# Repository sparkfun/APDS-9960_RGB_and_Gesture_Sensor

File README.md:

SparkFun APDS-9960 RGB and Gesture Sensor
========================================

[*SparkFun APDS-9960 Breakout Board (SEN-12787)*](https://www.sparkfun.com/products/12787)

This is the SparkFun RGB and Gesture Sensor, a small breakout board with a built in APDS-9960 sensor that offers ambient light and color measuring, proximity detection, and touchless gesture sensing.
With this RGB and Gesture Sensor you will be able to control a computer, microcontroller, robot, and more with a simple swipe of your hand! 

 Repository Contents
-------------------

* **/Hardware** - Eagle design files (.brd, .sch)
* **/Libraries** - Libraries for use with the SparkFun APDS9960 RGB and Gesture Sensor
* **/Production** - Production panel files (.brd)

Documentation
--------------
* **[Quickstart Guide](https://learn.sparkfun.com/tutorials/apds-9960-rgb-and-gesture-sensor-hookup-guide)** - Basic hookup guide for the sensor.
* **[Library/README](https://github.com/sparkfun/SparkFun_APDS-9960_Sensor_Arduino_Library/tree/V_1.4.1)** - Arduino library for the SparkFun_APDS9960 RGB and Gesture Sensor.
* **[SparkFun Fritzing repo](https://github.com/sparkfun/Fritzing_Parts)** - Fritzing diagrams for SparkFun products.
* **[SparkFun 3D Model repo](https://github.com/sparkfun/3D_Models)** - 3D models of SparkFun products. 

Product Versions
----------------
* **[SEN-12787](https://www.sparkfun.com/products/12787)** - APDS-9960 RGB and Gesture Sensor

Version History
---------------
* [V_H1.0_L1.4.2](https://github.com/sparkfun/APDS-9960_RGB_and_Gesture_Sensor/tree/V_H1.0_L1.4.2) - Fixing library name compiliation error. 
* [V_H1.0_L1.4.1](https://github.com/sparkfun/APDS-9960_RGB_and_Gesture_Sensor/tree/V_H1.0_L1.4.1) - Fixing minor typos in both library and hardware files.
* [V_1.1.1](https://github.com/sparkfun/APDS-9960_RGB_and_Gesture_Sensor/tree/V_1.1.1) - Updated to new tag syntax
* [V11](https://github.com/sparkfun/APDS-9960_RGB_and_Gesture_Sensor/tree/v11) - Updated to new library structure
* [v10](https://github.com/sparkfun/APDS-9960_RGB_and_Gesture_Sensor/tree/v10) - Release
* [v01](https://github.com/sparkfun/APDS-9960_RGB_and_Gesture_Sensor/tree/v01)

License Information
-------------------
This product is _**open source**_! 

The **hardware** is released under [Creative Commons ShareAlike 4.0 International](https://creativecommons.org/licenses/by-sa/4.0/).

The **code** is beerware; if you see me (or any other SparkFun employee) at the local, and you've found our code helpful, please buy us a round!

Please use, reuse, and modify these files as you see fit. Please maintain attribution to SparkFun Electronics and release anything derivative under the same license.

Distributed as-is; no warranty is given.

- Your friends at SparkFun.

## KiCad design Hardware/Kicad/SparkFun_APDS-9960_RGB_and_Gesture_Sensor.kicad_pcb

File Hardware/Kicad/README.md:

# What Are these Files?

These are Kicad hardware files, gerber files, and renders of the design. Created by [WyoLum](https://wyolum.com/).

# License

This product is open source! These Eagle files are released under the Creative Commons Share-Alike Attribution license ([CC BY-SA 3.0](http://creativecommons.org/licenses/by-sa/3.0/us/)).

Please use, reuse, and modify these files as you see fit. Please maintain attribution and release anything derivative under the same license.

- Your friends at SparkFun.

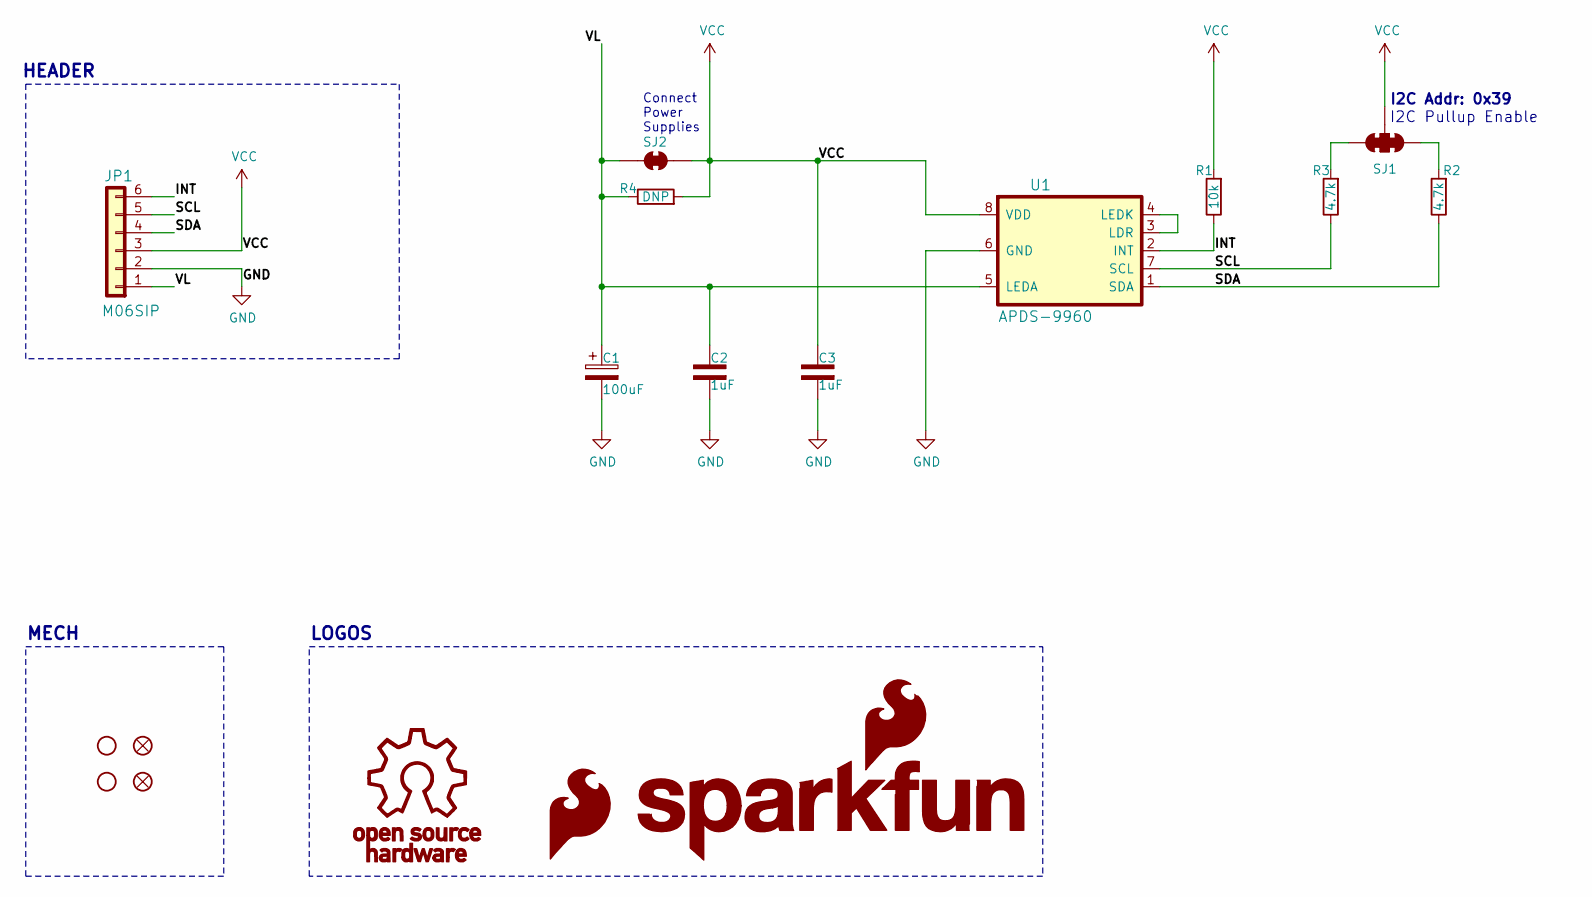
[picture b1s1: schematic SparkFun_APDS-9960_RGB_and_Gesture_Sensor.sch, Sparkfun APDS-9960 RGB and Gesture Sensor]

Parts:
C1: 100uF; c_2917
C2, C3: 1uF; 0603-CAP
FID1, FID2: FIDUCIAL1X2; FIDUCIAL-1X2
JP1: M06SIP; 1X06
LOGO1: SFE_LOGO_FLAME.1_INCH; SFE_LOGO_NAME_FLAME_.1
LOGO2: OSHW-LOGOS; OSHW-LOGO-S
R1: 10k; 0603-RES
R2, R3: 4.7k; 0603
R4: DNP; 0603-RES
SJ1: SOLDERJUMPER_2WAYPASTE1&2&3; SJ_3_PASTE1&2&3
SJ2: SOLDERJUMPERNC; SJ_2S
STANDOFF1, STANDOFF2: STAND-OFF
U1: APDS-9960
U$1: SFE_LOGO_NAME_FLAME.1_INCH; SFE_LOGO_FLAME_.1

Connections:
/INT: JP1.6, R1.1, U1.2 (INT)
/SCL: JP1.5, R3.1, U1.7 (SCL)
/SDA: JP1.4, R2.1, U1.1 (SDA)
/VL: C1.1, C2.1, JP1.1, R4.1, SJ2.1, U1.5 (LEDA)
GND: C1.2, C2.2, C3.2, JP1.2, U1.6 (GND)
unnamed: R2.2, SJ1.3
unnamed: R3.2, SJ1.1
unnamed: U1.3 (LDR), U1.4 (LEDK)
VCC: C3.1, JP1.3, R1.2, R4.2, SJ1.2, SJ2.2, U1.8 (VDD)

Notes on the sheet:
I2C Addr: 0x39
I2C Pullup Enable
Connect Power Supplies
MECH
LOGOS
HEADER

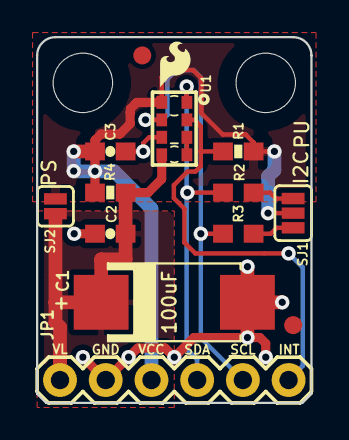
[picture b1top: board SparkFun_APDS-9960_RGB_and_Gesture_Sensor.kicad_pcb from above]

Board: 2 copper layers, 15.2 x 20.3 mm, 18 parts (0 on the bottom side), 9 nets.

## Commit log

2014-03-03 Added initial README and LICENSE files
2014-03-03 Created schematic for breakout board
2014-03-05 Created initial layout
2014-03-05 Added SS text
2014-03-05 Added name on layout
2014-03-05 Replaced 4.7k INT pullup with 10k
2014-03-12 Rotated OSHW logo and added I2C address to sch and silk.
2014-04-15 Test commit with account
2014-05-14 Added separate VLED (VL) pin, connected VL and VCC with solder jumper and optional resistor. Re-did layout to support new features.
2014-05-14 Fixed text font and size on schematic
2014-05-30 Added skeleton library
2014-05-30 Renamed library SFE_APDS-9960 to SFE_APDS9960
2014-06-04 Created skeleton library and ProximityTest example
2014-06-07 Added first part of init function. Still need to finish default register values.
2014-06-08 Added init code for prox and ALS registers
2014-06-09 Added led gain control and photodiode mask methods
2014-07-03 Updated library. Can now read gesture FIFO.
2014-07-06 Added readGesture method. It sorta works.
2014-07-06 Fixed gesture sensing. Works like the Avago demo now.
2014-07-07 Fixed gesture return values for U/D/L/R and gestureTest example.
2014-07-15 Updated version number to v10 for reds
2014-07-15 created panel v10
2014-10-15 Fixed buffer overflow issue with block reads. This fixed the problems with reading NEAR and FAR gestures.
2014-10-23 Added outline for color sensing code
2014-10-23 Moved several get/set methods to public. Added power on/off method.
2014-10-24 Added methods to control light sensor and light sensor demo sketch.
2014-10-27 Added color (RGB) light sensing example.
2014-10-27 Added methods for controlling ambient light interrupt thresholds.
2014-10-28 Finished interrupt demos for the library.
2014-10-28 Readme added to library
2014-10-28 Fixed some misspellings in the library readme.
2014-11-03 Added PDF of schematic
2014-11-04 Updated READMEs with license and folder information
2014-11-05 Changed the names of files and Arduino libraries to contain 'SparkFun_' as a prefix
2014-11-07 Added known issue to library regarding the freezing on fast gestures
2014-11-14 Fixed freezing issue with fast swipes
2014-11-18 Added pinMode like to GestureTest.ino example to fix interrupt not working with some Arduinos.
2014-12-15 Suggestions For Possible Board Revision
    I have a few suggestions to make this board work better in my
    application.
    I'm a noob with GitHub, so I appologise if I'm doing this wrong.
    Changes:
    1) Rotate and relocate sensor as close as possible to edge of board.
    Reason: I want to be able to put this sensor board into an enclosure
2015-01-14 Implemented disableProximitySensor()
2015-02-04 Changed 4.7k resistors to proper 0603-RES package.
    This adds a small silkscreen dot under the resistor.
2015-02-05 Reverting to current board layout files
2015-04-26 Squashed 'Libraries/Arduino/' content from commit cb761c9
    git-subtree-dir: Libraries/Arduino
    git-subtree-split: cb761c9f0f9f36acc54a8502904df46fbca3fc06
2015-04-26 Updated to new library structure
2015-04-29 Part of the new arduino lib format updates
2015-04-29 commited
2015-04-29 Squashed 'Libraries/Arduino/' content from commit d35b342
    git-subtree-dir: Libraries/Arduino
    git-subtree-split: d35b342f01b4587b4a9401d6ab1262f9d95b321b
2015-05-13 Squashed 'Libraries/Arduino/' changes from d35b342..e60af2c
    git-subtree-dir: Libraries/Arduino
    git-subtree-split: e60af2cdf0042a4ac6cdcac1a4fe5b38b0d575b7
2015-05-13 Updating documentation, adding git attributes
2015-07-21 Squashed 'Libraries/Arduino/' changes from e60af2c..347a7d5
    347a7d5 Updating library name
    git-subtree-dir: Libraries/Arduino
    git-subtree-split: 347a7d55f1cf009bff58c28733b1f0bd2172092e
2017-04-15 Fix the GestureTest example
    Resolve the interrupt number with digitalPinToInterrupt() instead of
    hardcoding it to "0". This is the recommended method from
    https://www.arduino.cc/en/Reference/attachInterrupt
    It should work with post-2014 releases of any Arduino IDE version.
    (1.0.x, 1.5.x, 1.6.x)
    Also declare the isr_flag as volatile. It will not make a difference
2017-07-10 Put Arduino library in its own folder
    The previous folder structure did not match the installation instructions found in the library's README.md file. The previous library folder name "Arduino" was very unhelpful.
2018-04-16 new panel
2019-06-08 Add GY-9960LLC APDS-9960 sensor support
2019-10-30 Fix issues 23 and 26
    https://github.com/sparkfun/APDS-9960_RGB_and_Gesture_Sensor/issues/26
    https://github.com/sparkfun/APDS-9960_RGB_and_Gesture_Sensor/issues/23
2020-06-04 fixing issue with Wire usage, finicky compilers throwing warnings, issue where gesture recognition fails if one diode pair is activated, issue where gesture recognition sometimes crashed esp based sy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
2020-06-09 changed attachInterrupt for Wemos boards
2020-12-22 Adding WyoLum's Kicad version.
2021-06-20 Update interrupt pin
2022-08-17 Fixed requestFrom() compilation error

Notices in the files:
Hardware/Kicad/SparkFun_APDS-9960_RGB_and_Gesture_Sensor.sch:
Released under the Creative Commons Attribution Share-Alike 4.0 License
parts and their libraries:
SparkFun-Aesthetics: Licensing: Creative Commons ShareAlike 4.0 International - https://creativecommons.org/licenses/by-sa/4.0
